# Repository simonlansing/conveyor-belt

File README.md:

# Miniature Conveyor Belt 

Miniature conveyor belt for simulation and having fun working with sensors and actuators, all controllable with Raspberry Pi. All sensors and actuators of the conveyor belt are connected to the GPIO pins of the Raspberry Pi via a separate circuit board. The board also contains a motor driver, a push button and three LEDs.

As simulation software [Node-RED](https://nodered.org/) is used locally on the Raspberry Pi. Based on this, the sensors and actuators could also be mapped as device shadows in the AWS IoT platform (Software follows :smile:).

## Components

The following components were used and can be screwed directly to the 3D-printed parts.

### Hardware

| No. | Name                                        | Quantity  | Notes             |
| :-: | :------------------------------------------ | :-------: | :---------------- |
| 1   | RFID reader RC522                           | 1         |                   |
| 2   | IR photoelectric switch barrier TRCT5000    | 1-3       |                   |
| 3   | Servo motor SG90                            | 1         |                   |
| 4   | Motor driver DRV8833                        | 1         |                   |
| 5   | TT motor DC3V-6V                            | 1         |                   |
| 6   | Raspberry Pi Camera Module                  | 1         |                   |
| 7   | Raspberry Pi 3/4                            | 1         |                   |
| 8   | Ball bearing 608 2RS 8x22x7 mm              | 2         | deflection roll   |
| 9   | Ball bearing 6800 zz 10x19x5                | 2         | drive roll        |
| 10  | Aluminium profile 20mm x 40mm x 290mm       | 1         |                   |
| 11  | Elastic band                                | 1         |                   |
| 12  | LEDs                                        | 3         |                   |
| 13  | Resistors for LEDs                          | 3         |                   |
| 14  | Push button                                 | 3         | see PCB           |

### Screws

| No. | Name                        | Quantity  | Notes             |
| :-: | :-------------------------- | :-------: | :---------------- |
| 1   | M3 x 8 countersunk screw    | 4         |                   |
| 2   | M3 x 10 countersunk screw   | 3         |                   |
| 3   | M3 x 12 countersunk screw   | 6         |                   |
| 4   | M4 x 10 countersunk screw   | 24        |                   |
| 5   | M4 x 12 countersunk screw   | 24        |                   |
| 6   | M3 x 5 flat headed screw    | 6         |                   |
| 7   | M3 x 10 flat headed screw   | 6         |                   |
| 8   | M3 x 12 flat headed screw   | 6         |                   |
| 9   | M3 x 18 flat headed screw   | 13        |                   |
| 10  | M3 x 25 flat headed screw   | 6         |                   |
| 11  | M2 spacer                   | 6         |                   |

### 3D printed parts

| No. | Name                            | Quantity  | Notes                             |
| :-: | :------------------------------ | :-------: | :-------------------------------- |
| 1   | box                             | 1         |                                   |
| 2   | camera mount                    | 1         |                                   |
| 3   | deflection roll                 | 1         |                                   |
| 4   | deflection roll mount           | 1         |                                   |
| 5   | deflection roll mount mirrored  | 1         |                                   |
| 6   | drive roll                      | 1         |                                   |
| 7   | foot                            | 2         |                                   |
| 8   | IR sensor mount                 | 1-2       | one servo is mounted on the motor |
| 9   | motor mount                     | 1         |                                   |
| 10  | motor mount mirrored            | 1         |                                   |
| 11  | servo lever                     | 1         |                                   |
| 12  | servo mount                     | 1         |                                   |

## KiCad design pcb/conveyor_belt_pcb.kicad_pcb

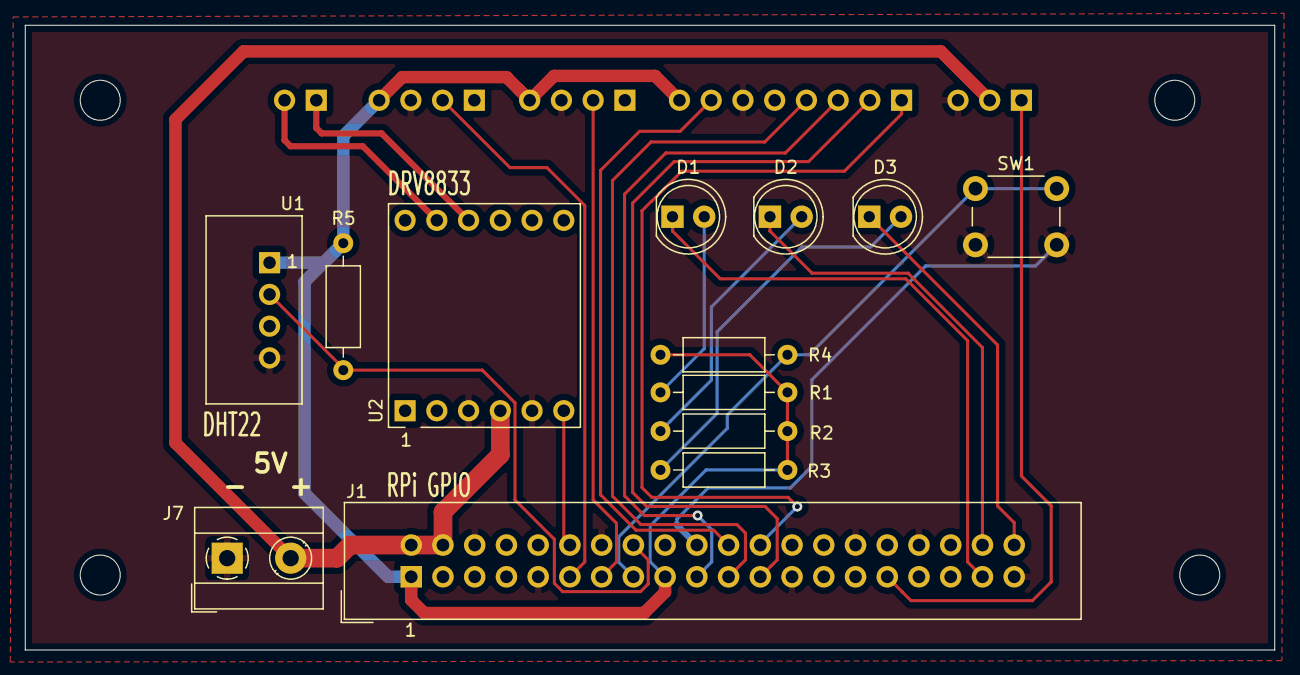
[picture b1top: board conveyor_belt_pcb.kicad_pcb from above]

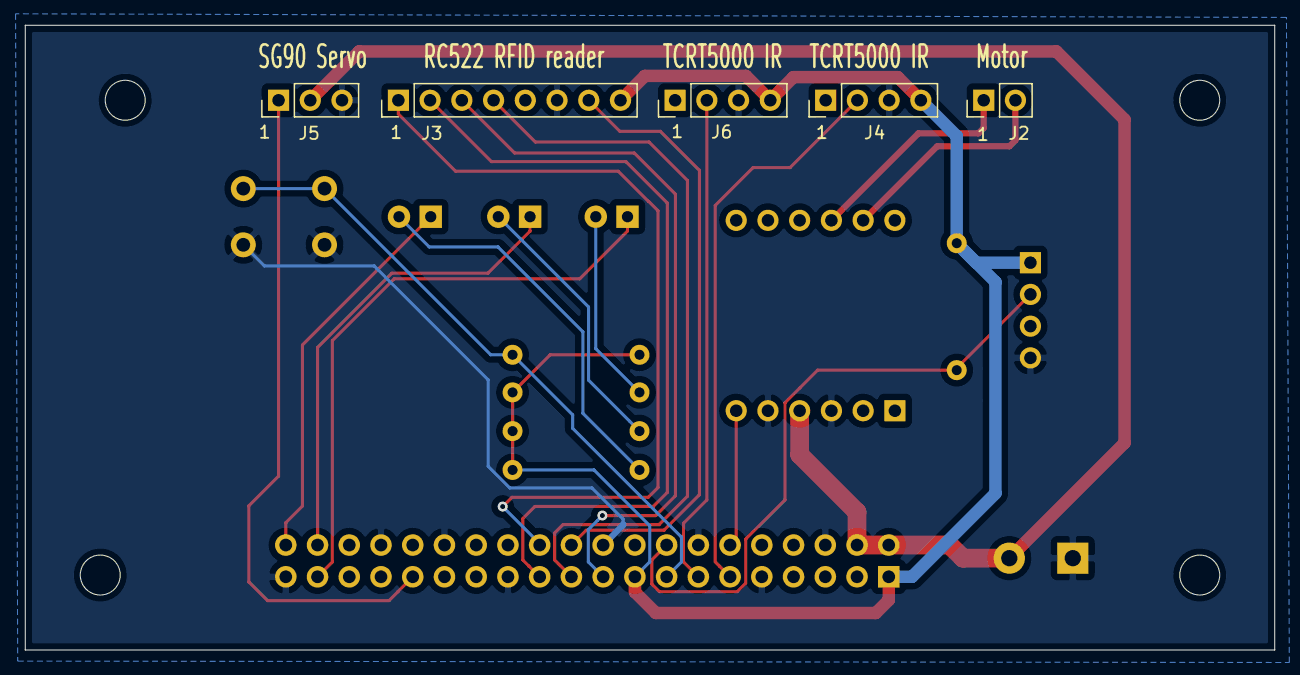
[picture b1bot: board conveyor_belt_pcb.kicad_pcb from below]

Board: 2 copper layers, 100.0 x 50.0 mm, 22 parts (5 on the bottom side), 22 nets.

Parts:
D1, D2, D3: LED; LED_D5.0mm
H1, H2, H3, H4: MountingHole; MountingHole_3.2mm_M3
J1: Raspberry_Pi_2_3; IDC-Header_2x20_P2.54mm_Vertical
J2: Conn_01x02_Male; PinHeader_1x02_P2.54mm_Vertical
J3: Conn_01x08_Male; PinHeader_1x08_P2.54mm_Vertical
J4, J6: Conn_01x04_Male; PinHeader_1x04_P2.54mm_Vertical
J5: Conn_01x03_Male; PinHeader_1x03_P2.54mm_Vertical
J7: Conn_01x02_Male; TerminalBlock_MetzConnect_Type101_RT01602HBWC_1x02_P5.08mm_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
R1, R2, R3: 130; R_Axial_DIN0207_L6.3mm_D2.5mm_P10.16mm_Horizontal
R4, R5: 4k7; R_Axial_DIN0207_L6.3mm_D2.5mm_P10.16mm_Horizontal
SW1: SW_Push; SW_PUSH_6mm_H5mm
U1: DHT11; DHT22
U2: DRV8833_board; DRV8833_BOARD_2x06_P2.54mm_Vertical

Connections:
+3V3: J1.1, J1.17, J3.8, J4.4, J6.4, R1.1, R2.1, R3.1, R4.2, R5.2, U1.1
+5V: J1.2, J1.4, J5.2, J7.2, U2.4
DHT22: J1.16, R5.1, U1.2
GND: J1.6, J1.9, J1.14, J1.20, J1.25, J1.30, J1.34, J1.39, J3.6, J4.3, J5.3, J6.3, J7.1, SW1.2, U1.4, U2.3, U2.5
L1: J1.13, J6.2
L2: J1.11, J4.2
LED1: D1.1, J1.37
LED2: D2.1, J1.38
LED3: D3.1, J1.40
unnamed: D1.2, R1.2
unnamed: D2.2, R2.2
unnamed: D3.2, R3.2
unnamed: J1.12, U2.6
unnamed: J2.1, U2.10
unnamed: J2.2, U2.11
RFID_CS: J1.24, J3.1
RFID_MISO: J1.21, J3.4
RFID_MOSI: J1.19, J3.3
RFID_RST: J1.22, J3.7
RFID_SCK: J1.23, J3.2
Servo: J1.31, J5.1
Switch: J1.15, R4.1, SW1.1

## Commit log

2020-10-14 Added baseline files
2020-10-14 updated table numbering
